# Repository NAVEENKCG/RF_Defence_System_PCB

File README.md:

The Above files are PCB design which i have done a project of Defence System using Radio Frequency concept. The Board is designed as per the same circuit in the hardware project.

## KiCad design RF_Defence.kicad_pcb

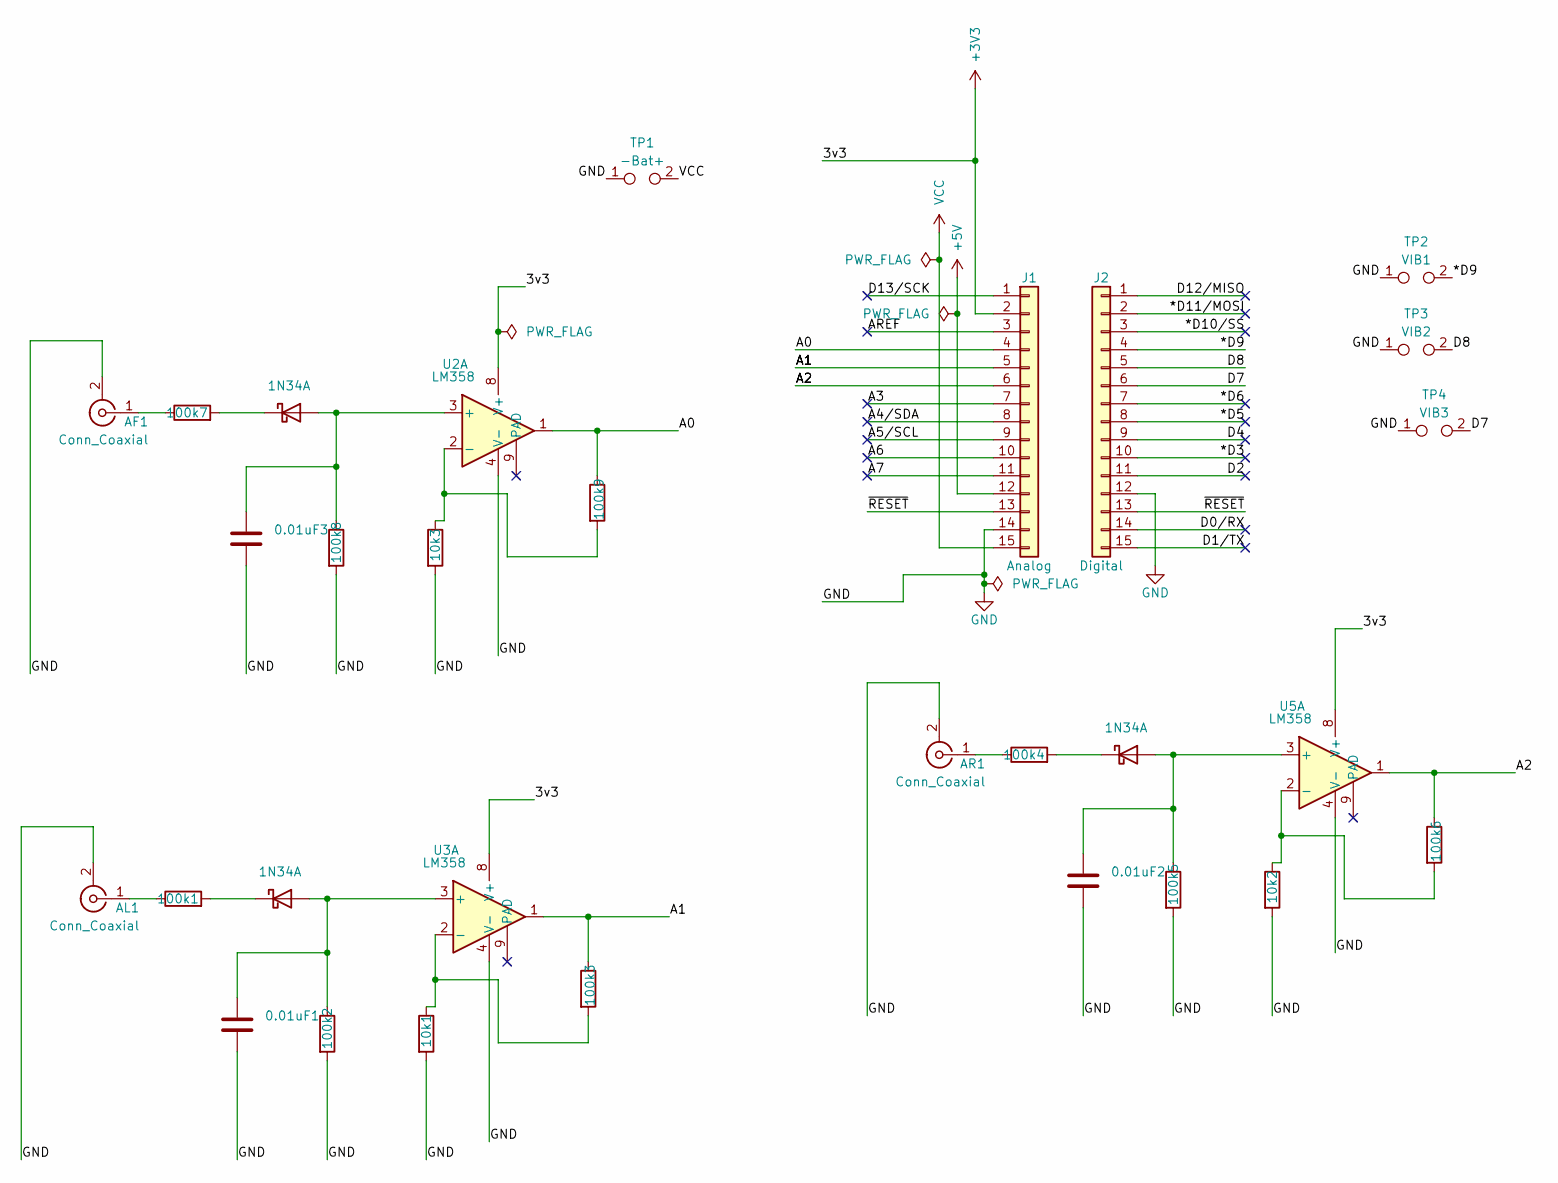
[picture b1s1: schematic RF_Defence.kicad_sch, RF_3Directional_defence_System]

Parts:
0.01uF1, 0.01uF2, 0.01uF3: C; C_Disc_D3.0mm_W1.6mm_P2.50mm
10k1, 10k2, 10k3, 100k1, 100k2, 100k3, 100k4, 100k5, 100k6, 100k7, 100k8, 100k9: R; R_Axial_DIN0204_L3.6mm_D1.6mm_P5.08mm_Horizontal
AF1: Conn_Coaxial; SMA_Amphenol_132291_Vertical
AL1: Conn_Coaxial; SMA_Amphenol_132291_Vertical
AR1: Conn_Coaxial; SMA_Amphenol_132291_Vertical
D1, D2, D3: 1N34A; D_DO-35_SOD27_P7.62mm_Horizontal
J1: Analog; PinHeader_1x15_P2.54mm_Vertical
J2: Digital; PinHeader_1x15_P2.54mm_Vertical
TP1: -Bat+; PinHeader_1x02_P2.54mm_Vertical
TP2: VIB1; PinHeader_1x02_P2.54mm_Vertical
TP3: VIB2; PinHeader_1x02_P2.54mm_Vertical
TP4: VIB3; PinHeader_1x02_P2.54mm_Vertical
U1, U4, U6: LM358_DFN; DFN-8-1EP_2x2mm_P0.5mm_EP1.05x1.75mm
U2, U3, U5: LM358; DIP-8_W7.62mm

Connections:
+3V3: J1.2, U1.8 (V+), U4.8 (V+), U6.8 (V+)
+5V: J1.12
/*D3: J2.10
/*D5: J2.8
/*D6: J2.7
/*D9: J2.4, TP2.2
/*D10/SS: J2.3
/*D11/MOSI: J2.2
/A0: 100k9.1, J1.4, U2.1
/A1: 100k3.1, J1.5, U3.1
/A2: 100k6.1, J1.6, U5.1
/A3: J1.7
/A4/SDA: J1.8
/A5/SCL: J1.9
/A6: J1.10
/A7: J1.11
/AREF: J1.3
/D0/RX: J2.14
/D1/TX: J2.15
/D2: J2.11
/D4: J2.9
/D7: J2.6, TP4.2
/D8: J2.5, TP3.2
/D12/MISO: J2.1
/D13/SCK: J1.1
/~RESET: J1.13, J2.13
GND: 0.01uF1.2, 0.01uF2.2, 0.01uF3.2, 10k1.2, 10k2.2, 10k3.2, 100k2.2, 100k5.2, 100k8.2, AF1.2 (Ext), AL1.2 (Ext), AR1.2 (Ext), J1.14, J2.12, TP1.1, TP2.1, TP3.1, TP4.1, U1.4 (V-), U4.4 (V-), U6.4 (V-)
unnamed: 100k7.1, AF1.1 (In)
unnamed: 100k1.1, AL1.1 (In)
unnamed: 100k4.1, AR1.1 (In)
unnamed: 0.01uF3.1, 100k8.1, D1.2 (A), U2.3 (+)
unnamed: 100k7.2, D1.1 (K)
unnamed: 0.01uF1.1, 100k2.1, D2.2 (A), U3.3 (+)
unnamed: 100k1.2, D2.1 (K)
unnamed: 0.01uF2.1, 100k5.1, D3.2 (A), U5.3 (+)
unnamed: 100k4.2, D3.1 (K)
unnamed: 10k3.1, 100k9.2, U2.2 (-)
unnamed: 10k1.1, 100k3.2, U3.2 (-)
unnamed: 10k2.1, 100k6.2, U5.2 (-)
VCC: J1.15, TP1.2

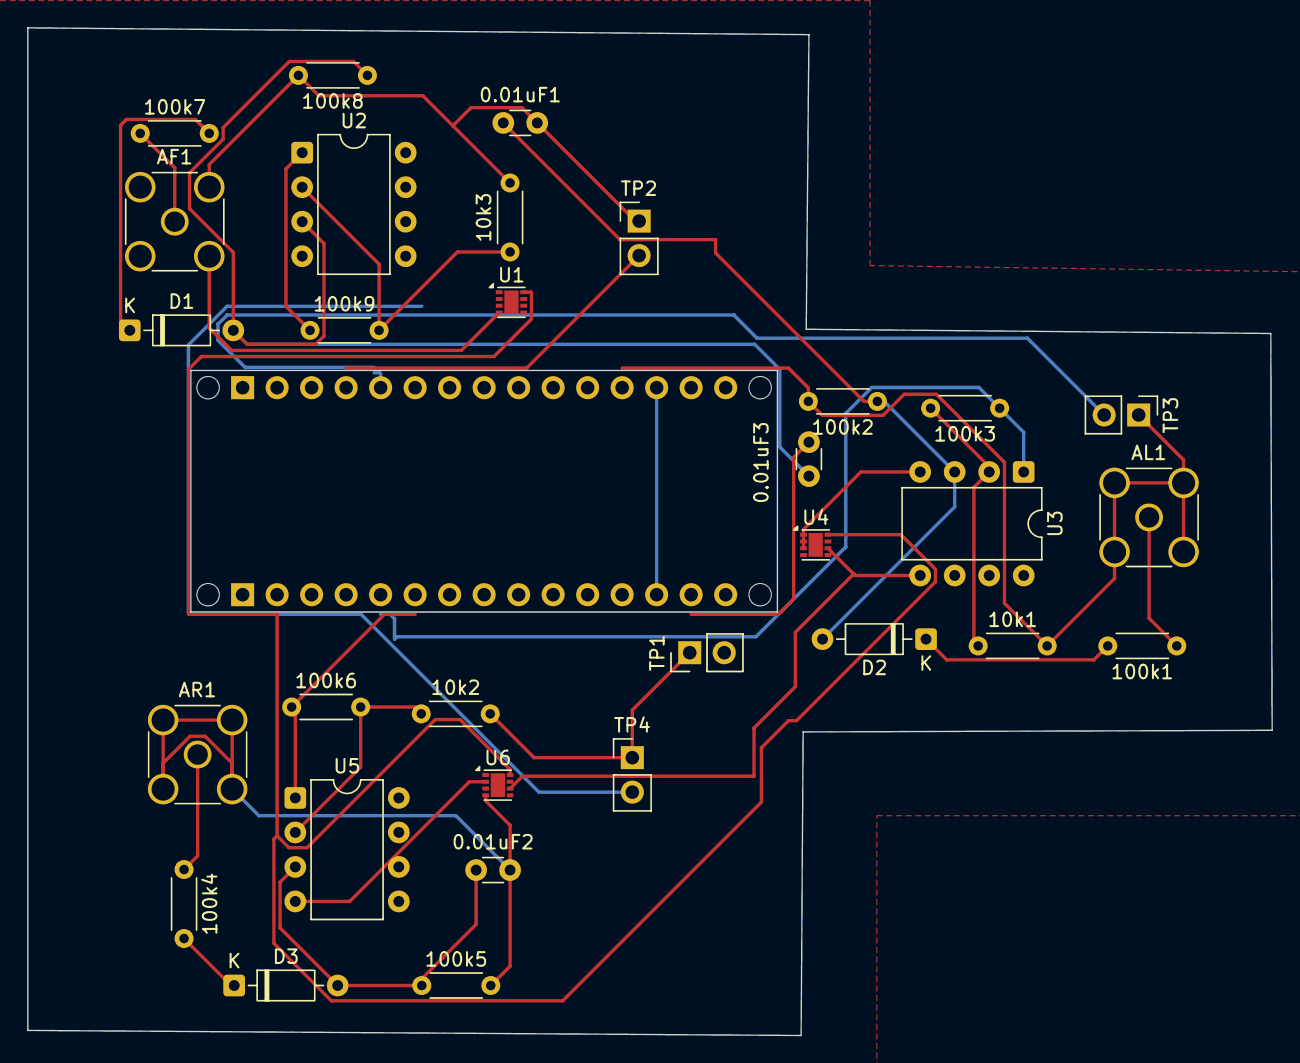
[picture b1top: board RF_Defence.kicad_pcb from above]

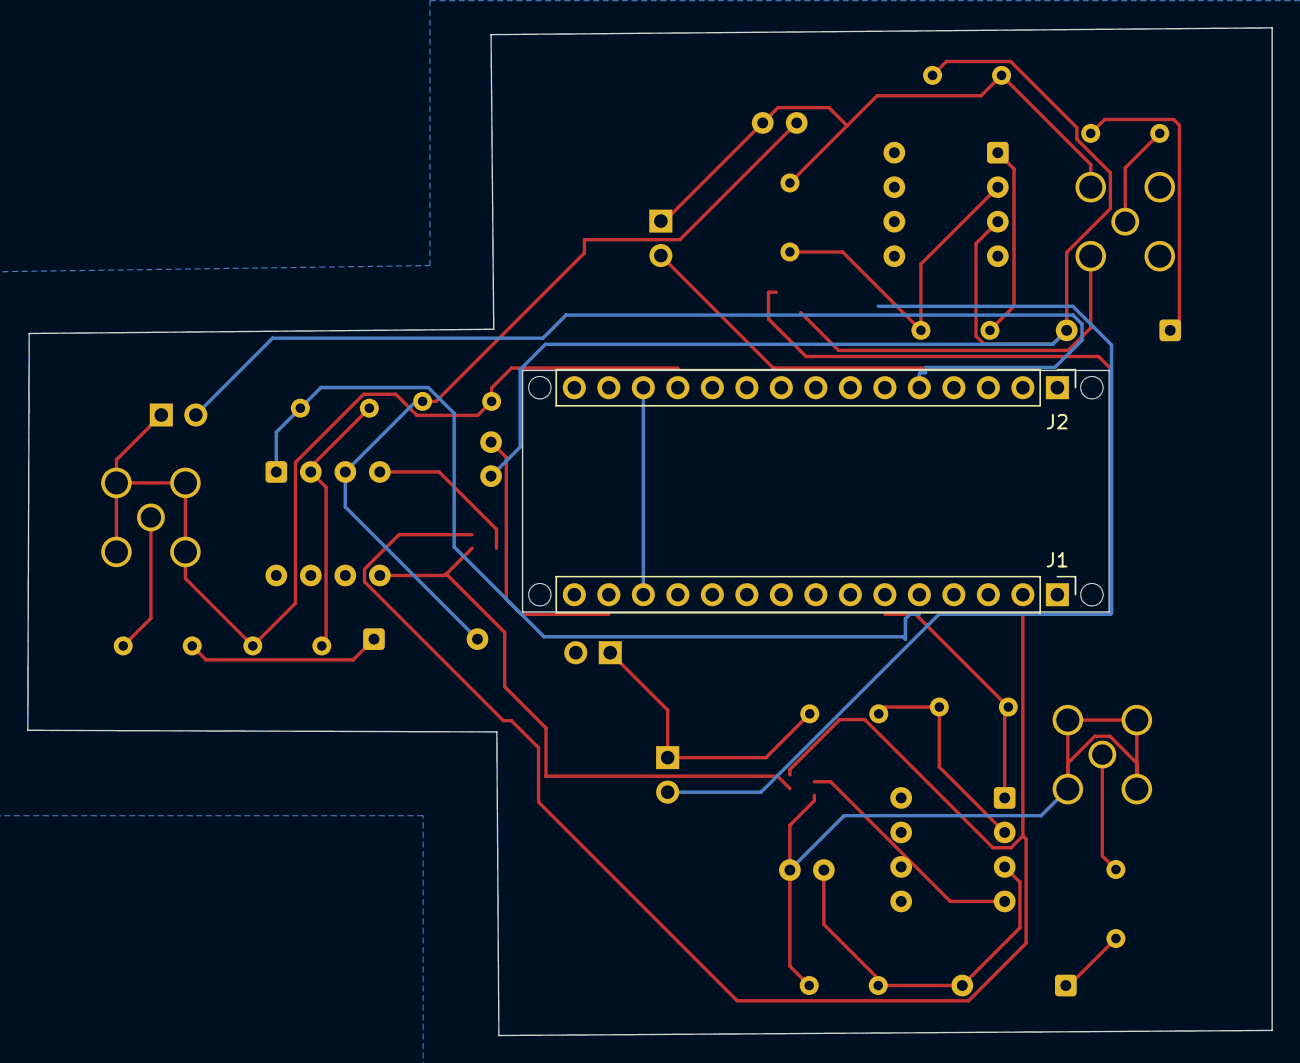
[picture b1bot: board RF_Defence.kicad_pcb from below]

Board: 2 copper layers, 91.6 x 74.2 mm, 37 parts (2 on the bottom side), 22 nets.

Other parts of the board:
MH1, MH2, MH3, MH4: MountingHole_65mil

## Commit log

2026-04-29 Add project description for PCB design
